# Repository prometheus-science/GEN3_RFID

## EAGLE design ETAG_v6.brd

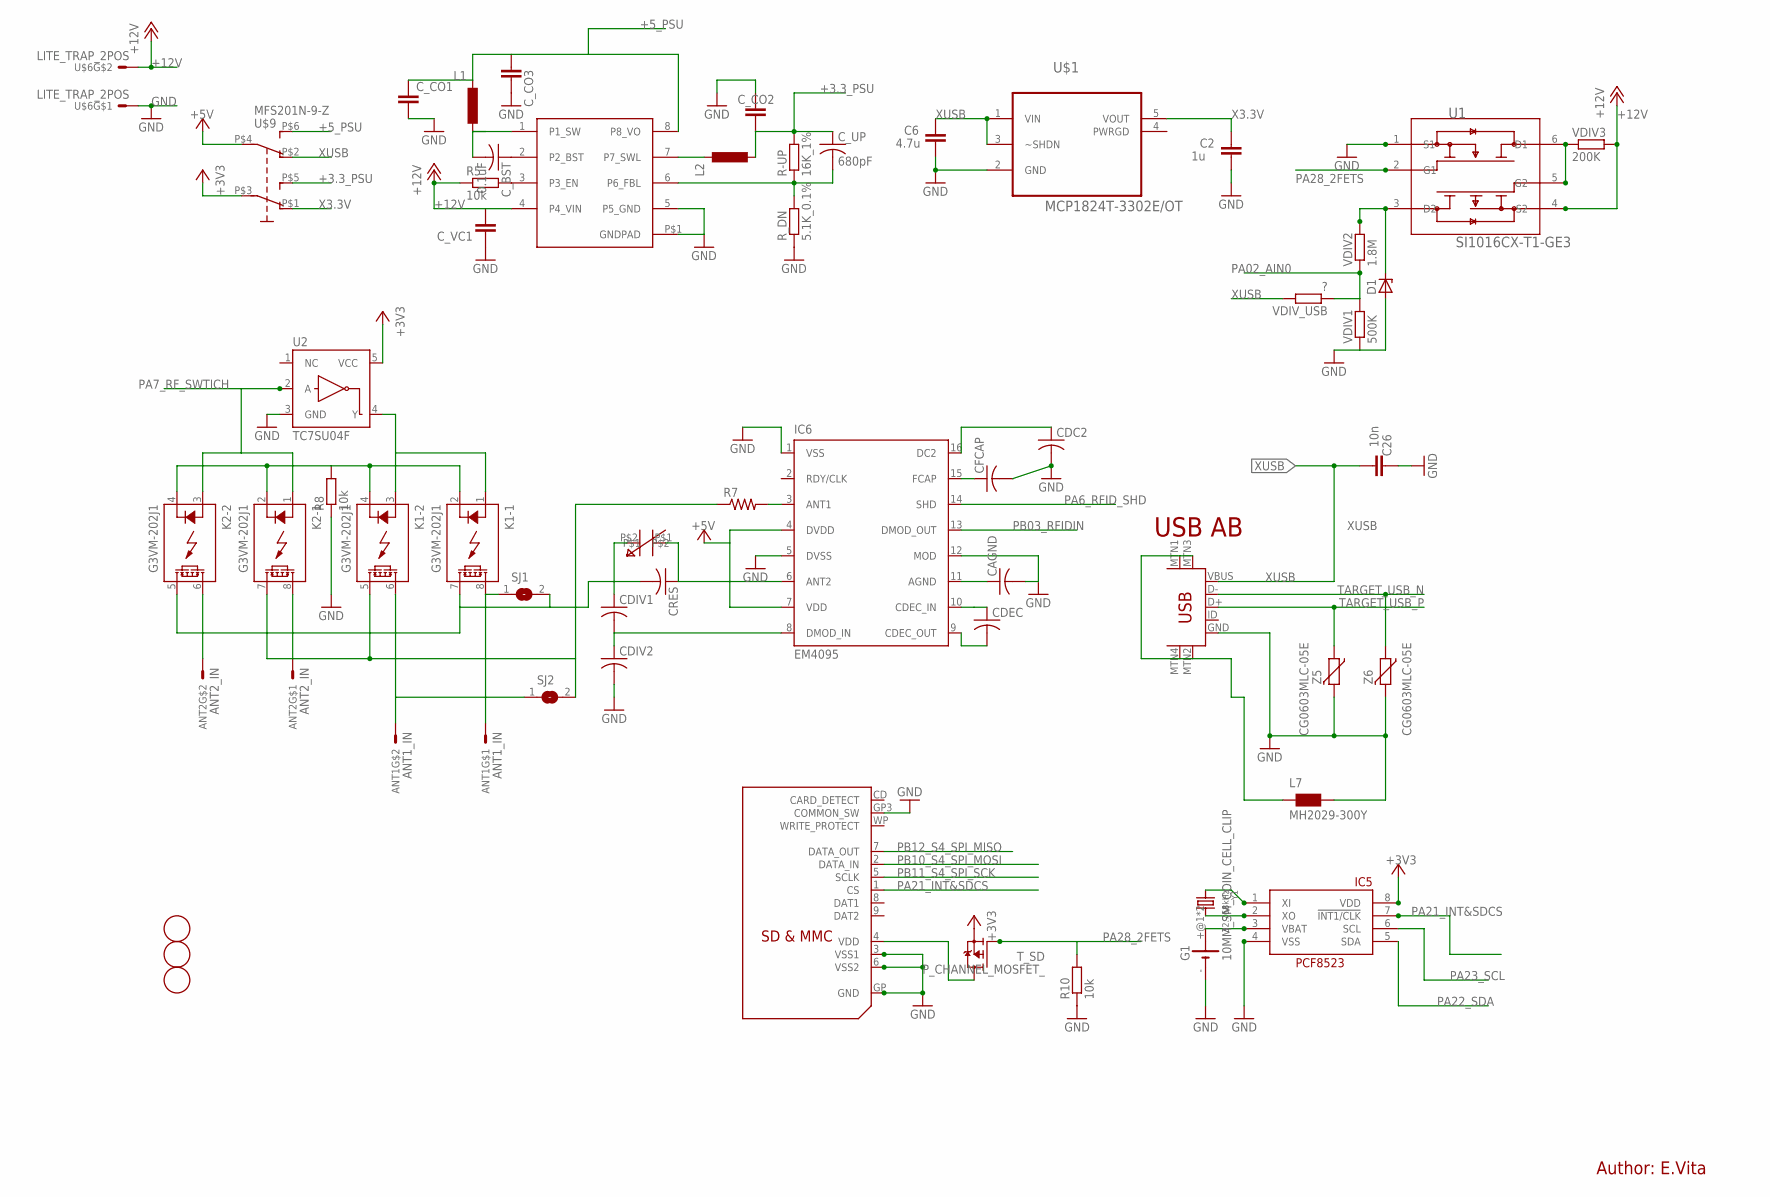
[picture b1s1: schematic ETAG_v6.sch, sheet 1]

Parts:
ANT1: ANT1_IN; LITE_TRAP_MINI
ANT2: ANT2_IN; LITE_TRAP_MINI
C2: 1u; C0603-ROUND
C6: 4.7u; C0603-ROUND
C26: 10n; C0603-ROUND
CAGND: C-US; C0603-ROUND
CDC2: C-US; C0603-ROUND
CDEC: C-US; C0603-ROUND
CDIV1, CDIV2: C-USC1206K; C1206K
CFCAP: C-US; C0603-ROUND
CRES: C-USC1206K; C1206K
C_BST: 0.1uF; C0603-ROUND
C_CO1, C_CO2: 22uF; C0805
C_CO3: 10uF; C0805
C_UP: 680pF; C0603-ROUND
C_VC1: 10uF; C1210
D1: ZENER-DIODESOD123; SOD123FL
FD1, FD2, FD3: FIDUCIALMOUNT; FIDUCIA-MOUNT
G1: 10MM_SM_COIN_CELL_CLIP
IC5: RTC_PCF8523T; SOIC8_150MIL
IC6: EM4095; SO16
K1, K2: G3VM-202J1; SOP08
L1: 22uH; SLF10165
L2: 2.2uH; L1008(2520METRIC)
L7: MH2029-300Y; 0805
R5, R8, R10: 10k; R0603-ROUND
R7: R-US_R1206; R1206
R-UP: 16K_1%; R0603-ROUND
R_DN: 5.1K_0.1%; R0603-ROUND
SJ1, SJ2: SJW
T_SD: P_CHANNEL_MOSFET_; SOT23
U1: SI1016CX-T1-GE3; SOT50P162X60-6N
U2: TC7SU04F; SOT23-5
U$1: MCP1824T-3302E/OT; SOT95P270X145-5N
U$3: BD93291EFJSOP8_W_GND; SOP08_GNDPAD
U$4: SDMMC06132; 06132
U$5: USB-MINIB-5PIN; USB-MINIB
U$6: LITE_TRAP_2POS; LITE_TRAP_MINI
U$9: MFS201N-9-Z
VAR_C: TZB4Z100AB10R00
VDIV1: 500K; R0603-ROUND
VDIV2: 1.8M; R0603-ROUND
VDIV3: 200K; R0603-ROUND
VDIV_USB: ?; R0603-ROUND
Y1: 32.768kHz; CRYSTAL_8X3.8
Z5, Z6: CG0603MLC-05E; CT/CN0603

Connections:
2GND: L7.1, U$5.MTN1 (MTN2), U$5.MTN2 (MTN3), U$5.MTN3 (MTN1), U$5.MTN4
+3.3_PSU: C_CO2.2, C_UP.1, L2.2, R-UP.2, U$9.P$5 (S)
+3V3: IC5.8 (VDD), T_SD.2 (S), U2.5 (VCC), U$9.P$3; also elsewhere on the board
+5V: IC6.4 (DVDD), IC6.7 (VDD), U$9.P$4 (P1); also elsewhere on the board
+5_PSU: C_CO1.1, C_CO3.1, L1.P$1 (1), U$3.8 (P8_VO), U$9.P$6 (S1)
+12V: C_VC1.2, R5.1, U1.4 (S2), U$3.4 (P4_VIN), U$6.P$3, U$6.P$4, VDIV3.2; also elsewhere on the board
GND: C2.1, C6.1, C26.2, CAGND.2, CDC2.2, CDIV2.2, CFCAP.2, C_CO1.2, C_CO2.1, C_CO3.2, C_VC1.1, D1.A, G1.-, IC5.4 (VSS), IC6.1 (VSS), IC6.5 (DVSS), IC6.12 (MOD), L7.2, R8.1, R10.1, R_DN.1, U1.1 (S1), U2.3 (GND), U$1.2 (GND), U$3.5 (P5_GND), U$3.P$1 (GNDPAD), U$4.3 (VSS1), U$4.6 (VSS2), U$4.GP (GND), U$4.GP3 (COMMON_SW), U$5.GND, U$6.P$1, U$6.P$2, VDIV1.1, Z5.2, Z6.2; also elsewhere on the board
unnamed: IC5.2 (XO), Y1.P$4 (2)
unnamed: IC5.1 (XI), Y1.P$1 (1)
unnamed: CFCAP.1, IC6.15 (FCAP)
unnamed: CAGND.1, IC6.11 (AGND)
unnamed: C_BST.1, U$3.2 (P2_BST)
unnamed: C_UP.2, R-UP.1, R_DN.2, U$3.6 (P6_FBL)
unnamed: R5.2, U$3.3 (P3_EN)
unnamed: K1.5 (D2), K2.7 (D2), R7.1, SJ2.2
unnamed: CDIV1.1, CRES.2, K1.7 (D2), K2.5 (D2), SJ1.2, VAR_C.P$2
unnamed: CRES.1, IC6.6 (ANT2), VAR_C.P$1
unnamed: CDIV1.2, CDIV2.1, IC6.8 (DMOD_IN)
unnamed: ANT1.P$1, ANT1.P$2, K1.8 (D1), SJ1.1
unnamed: U1.5 (G2), U1.6 (D1), VDIV3.1
unnamed: ANT2.P$1, ANT2.P$2, K2.8 (D1)
unnamed: CDC2.1, IC6.16 (DC2)
unnamed: CDEC.2, IC6.9 (CDEC_OUT)
unnamed: CDEC.1, IC6.10 (CDEC_IN)
unnamed: IC6.3 (ANT1), R7.2
unnamed: D1.C, U1.3 (D2), VDIV2.2
unnamed: K1.2 (K), K1.4 (K), K2.2 (K), K2.4 (K), R8.2
unnamed: L2.1, U$3.7 (P7_SWL)
unnamed: C_BST.2, L1.P$2 (2), U$3.1 (P1_SW)
unnamed: ANT2.P$3, ANT2.P$4, K2.6 (D1)
unnamed: K1.1 (A), K1.3 (A), U2.4 (Y)
unnamed: ANT1.P$3, ANT1.P$4, K1.6 (D1), SJ2.1
PA02_AIN0: VDIV1.2, VDIV2.1, VDIV_USB.1; also elsewhere on the board
PA6_RFID_SHD: IC6.14 (SHD)
PA7_RF_SWTICH: K2.1 (A), K2.3 (A), U2.2 (A); also elsewhere on the board
PA21_INT&SDCS: IC5.7 (!INT1/CLK), U$4.1 (CS); also elsewhere on the board
PA22_SDA: IC5.5 (SDA); also elsewhere on the board
PA23_SCL: IC5.6 (SCL); also elsewhere on the board
PA28_2FETS: R10.2, T_SD.1 (G), U1.2 (G1); also elsewhere on the board
PB03_RFIDIN: IC6.13 (DMOD_OUT); also elsewhere on the board
PB10_S4_SPI_MOSI: U$4.2 (DATA_IN); also elsewhere on the board
PB11_S4_SPI_SCK: U$4.5 (SCLK); also elsewhere on the board
PB12_S4_SPI_MISO: U$4.7 (DATA_OUT); also elsewhere on the board
TARGET_USB_N: U$5.D-, Z6.1; also elsewhere on the board
TARGET_USB_P: U$5.D+, Z5.1; also elsewhere on the board
VBAT1: G1.+@1 (+), G1.+@2 (+), IC5.3 (VBAT)
VDD: T_SD.3 (D), U$4.4 (VDD)
X3.3V: C2.2, U$1.5 (VOUT), U$9.P$1 (O)
XUSB: C6.2, C26.1, U$1.1 (VIN), U$1.3 (~SHDN), U$5.VBUS, U$9.P$2 (O1), VDIV_USB.2

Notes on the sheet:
USB AB
Author: E.Vita

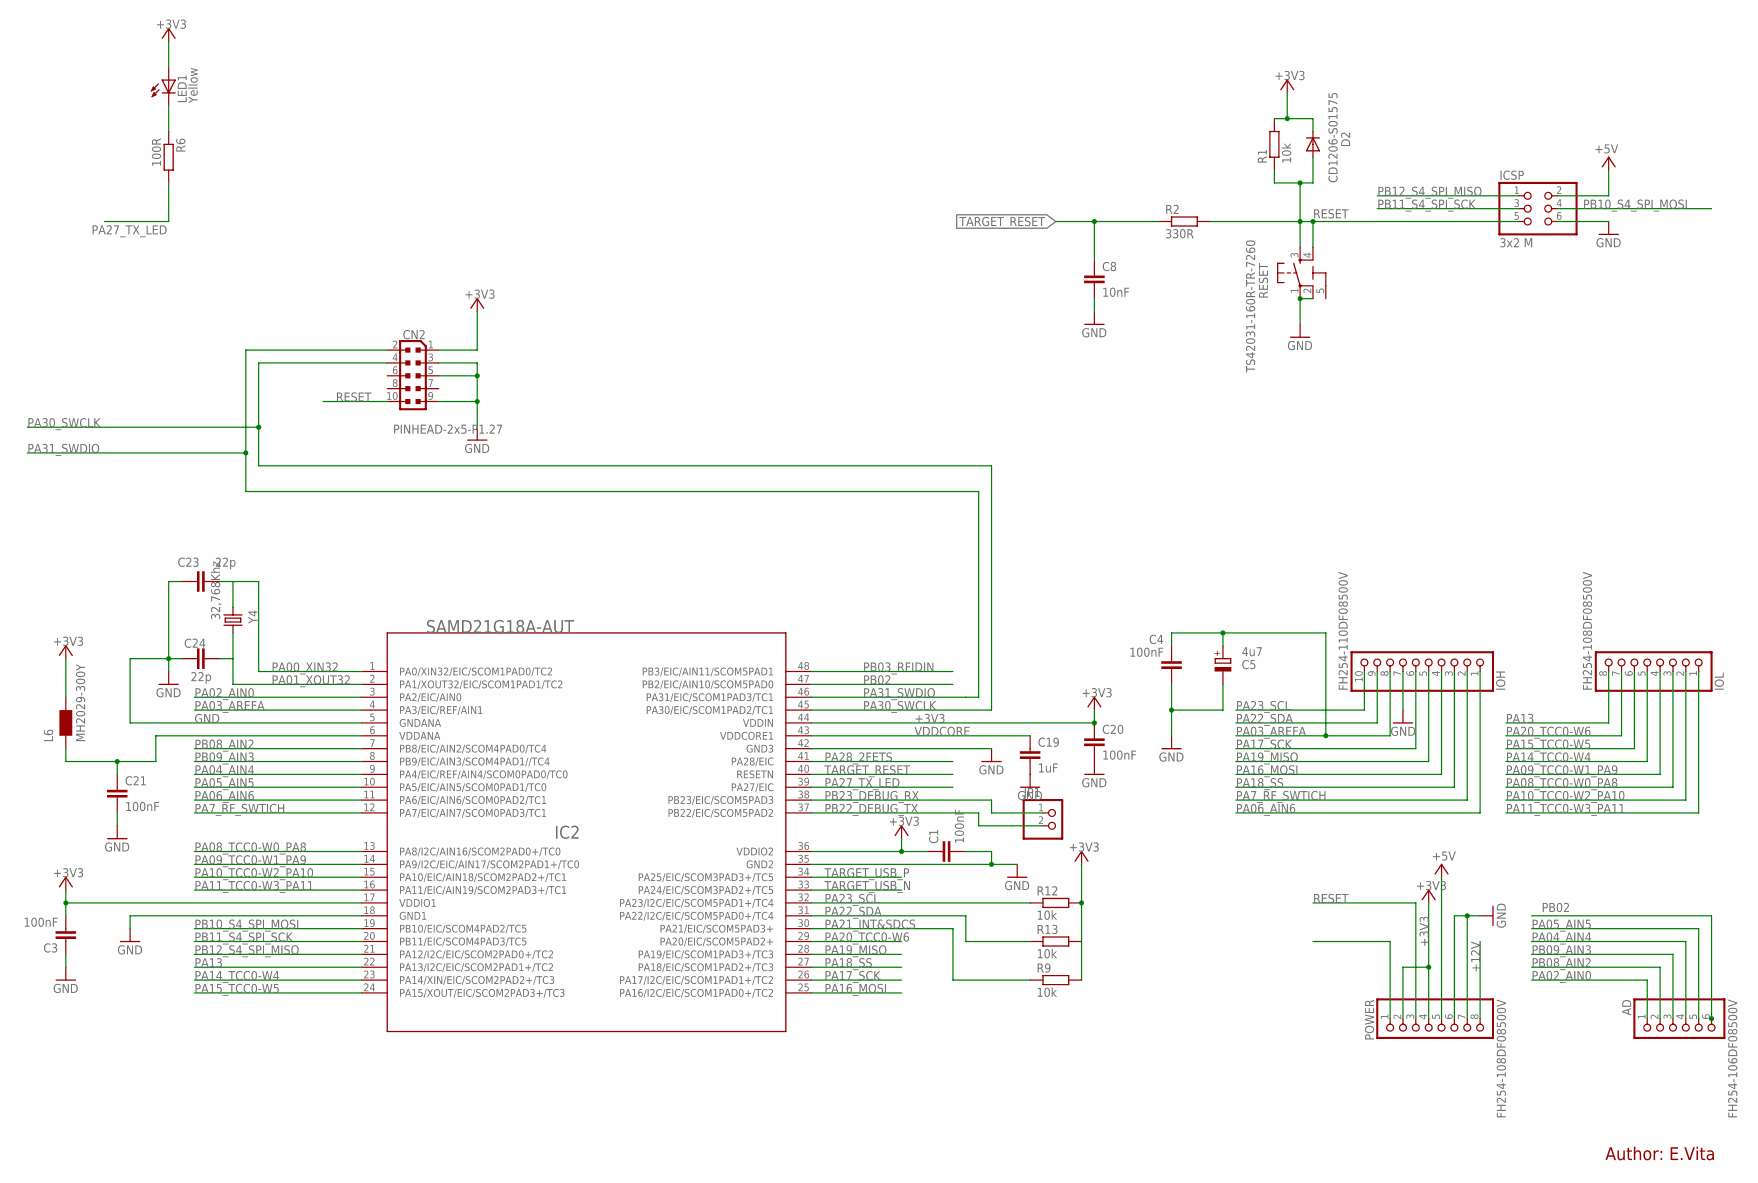
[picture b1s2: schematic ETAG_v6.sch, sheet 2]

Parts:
AD: FH254-106DF08500V; 1X06
C1, C3, C4, C20, C21: 100nF; C0603-ROUND
C5: 4u7; SMC_A
C8: 10nF; C0603-ROUND
C19: 1uF; C0603-ROUND
C23, C24: 22p; C0603-ROUND
CN2: PINHEAD-2x5-P1.27; PINHEAD_2X05_127
D2: CD1206-S01575; MINIMELF
IC2: SAMD21G18A-AUT; TQFP48-7X7
ICSP: 3x2 M; 2X03
IOH: FH254-110DF08500V; 1X10
IOL: FH254-108DF08500V; 1X08
JP1: PINHD-1X2; 1X02
L6: MH2029-300Y; 0805
LED1: Yellow; CHIPLED_0805
POWER: FH254-108DF08500V; 1X08
R1, R9, R12, R13: 10k; R0603-ROUND
R2: 330R; R0603-ROUND
R6: 100R; R0603-ROUND
RESET: TS42031-160R-TR-7260; TS42
Y4: 32,768Khz; RESONATOR_EPSON_FC_145

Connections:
5-GND: RESET.5 (5-GND)
+3V3: C1.1, C3.2, C20.1, CN2.1, D2.C, IC2.17 (VDDIO1), IC2.36 (VDDIO2), IC2.44 (VDDIN), L6.2, LED1.A, POWER.2, POWER.4, R1.2, R9.2, R12.2, R13.2; also elsewhere on the board
+5V: ICSP.2, POWER.5; also elsewhere on the board
+12V: POWER.8; also elsewhere on the board
GND: C1.2, C3.1, C4.2, C5.-, C8.2, C19.2, C20.2, C21.2, C23.1, C24.1, CN2.3, CN2.5, CN2.9, IC2.5 (GNDANA), IC2.18 (GND1), IC2.35 (GND2), IC2.42 (GND3), ICSP.6, IOH.7, POWER.6, POWER.7, RESET.1, RESET.2; also elsewhere on the board
unnamed: LED1.C, R6.1
unnamed: C21.1, IC2.6 (VDDANA), L6.1
PA00_XIN32: C23.2, IC2.1 (PA0/XIN32/EIC/SCOM1PAD0/TC2), Y4.P$1 (1)
PA01_XOUT32: C24.2, IC2.2 (PA1/XOUT32/EIC/SCOM1PAD1/TC2), Y4.P$2 (2)
PA02_AIN0: AD.1, IC2.3 (PA2/EIC/AIN0); also elsewhere on the board
PA03_AREFA: C4.1, C5.+, IC2.4 (PA3/EIC/REF/AIN1), IOH.8
PA04_AIN4: AD.4, IC2.9 (PA4/EIC/REF/AIN4/SCOM0PAD0/TC0)
PA05_AIN5: AD.5, IC2.10 (PA5/EIC/AIN5/SCOM0PAD1/TC0)
PA06_AIN6: IC2.11 (PA6/EIC/AIN6/SCOM0PAD2/TC1), IOH.1
PA7_RF_SWTICH: IC2.12 (PA7/EIC/AIN7/SCOM0PAD3/TC1), IOH.2; also elsewhere on the board
PA08_TCC0-W0_PA8: IC2.13 (PA8/I2C/AIN16/SCOM2PAD0+/TC0), IOL.3
PA09_TCC0-W1_PA9: IC2.14 (PA9/I2C/EIC/AIN17/SCOM2PAD1+/TC0), IOL.4
PA10_TCC0-W2_PA10: IC2.15 (PA10/EIC/AIN18/SCOM2PAD2+/TC1), IOL.2
PA11_TCC0-W3_PA11: IC2.16 (PA11/EIC/AIN19/SCOM2PAD3+/TC1), IOL.1
PA13: IC2.22 (PA13/I2C/EIC/SCOM2PAD1+/TC2), IOL.8
PA14_TCC0-W4: IC2.23 (PA14/XIN/EIC/SCOM2PAD2+/TC3), IOL.5
PA15_TCC0-W5: IC2.24 (PA15/XOUT/EIC/SCOM2PAD3+/TC3), IOL.6
PA16_MOSI: IC2.25 (PA16/I2C/EIC/SCOM1PAD0+/TC2), IOH.4
PA17_SCK: IC2.26 (PA17/I2C/EIC/SCOM1PAD1+/TC2), IOH.6
PA18_SS: IC2.27 (PA18/EIC/SCOM1PAD2+/TC3), IOH.3
PA19_MISO: IC2.28 (PA19/EIC/SCOM1PAD3+/TC3), IOH.5
PA20_TCC0-W6: IC2.29 (PA20/EIC/SCOM5PAD2+), IOL.7
PA21_INT&SDCS: IC2.30 (PA21/EIC/SCOM5PAD3+), R9.1; also elsewhere on the board
PA22_SDA: IC2.31 (PA22/I2C/EIC/SCOM5PAD0+/TC4), IOH.9, R13.1; also elsewhere on the board
PA23_SCL: IC2.32 (PA23/I2C/EIC/SCOM5PAD1+/TC4), IOH.10, R12.1; also elsewhere on the board
PA27_TX_LED: IC2.39 (PA27/EIC), R6.2
PA28_2FETS: IC2.41 (PA28/EIC); also elsewhere on the board
PA30_SWCLK: CN2.4, IC2.45 (PA30/EIC/SCOM1PAD2/TC1)
PA31_SWDIO: CN2.2, IC2.46 (PA31/EIC/SCOM1PAD3/TC1)
PB02: AD.6, IC2.47 (PB2/EIC/AIN10/SCOM5PAD0)
PB03_RFIDIN: IC2.48 (PB3/EIC/AIN11/SCOM5PAD1); also elsewhere on the board
PB08_AIN2: AD.2, IC2.7 (PB8/EIC/AIN2/SCOM4PAD0/TC4)
PB09_AIN3: AD.3, IC2.8 (PB9/EIC/AIN3/SCOM4PAD1//TC4)
PB10_S4_SPI_MOSI: IC2.19 (PB10/EIC/SCOM4PAD2/TC5), ICSP.4; also elsewhere on the board
PB11_S4_SPI_SCK: IC2.20 (PB11/EIC/SCOM4PAD3/TC5), ICSP.3; also elsewhere on the board
PB12_S4_SPI_MISO: IC2.21 (PA12/I2C/EIC/SCOM2PAD0+/TC2), ICSP.1; also elsewhere on the board
PB22_DEBUG_TX: IC2.37 (PB22/EIC/SCOM5PAD2), JP1.2
PB23_DEBUG_RX: IC2.38 (PB23/EIC/SCOM5PAD3), JP1.1
RESET: CN2.10, D2.A, ICSP.5, POWER.3, R1.1, R2.2, RESET.3, RESET.4
TARGET_RESET: C8.1, IC2.40 (RESETN), R2.1
TARGET_USB_N: IC2.33 (PA24/EIC/SCOM3PAD2+/TC5); also elsewhere on the board
TARGET_USB_P: IC2.34 (PA25/EIC/SCOM3PAD3+/TC5); also elsewhere on the board
VDDCORE: C19.1, IC2.43 (VDDCORE1)

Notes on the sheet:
Author: E.Vita

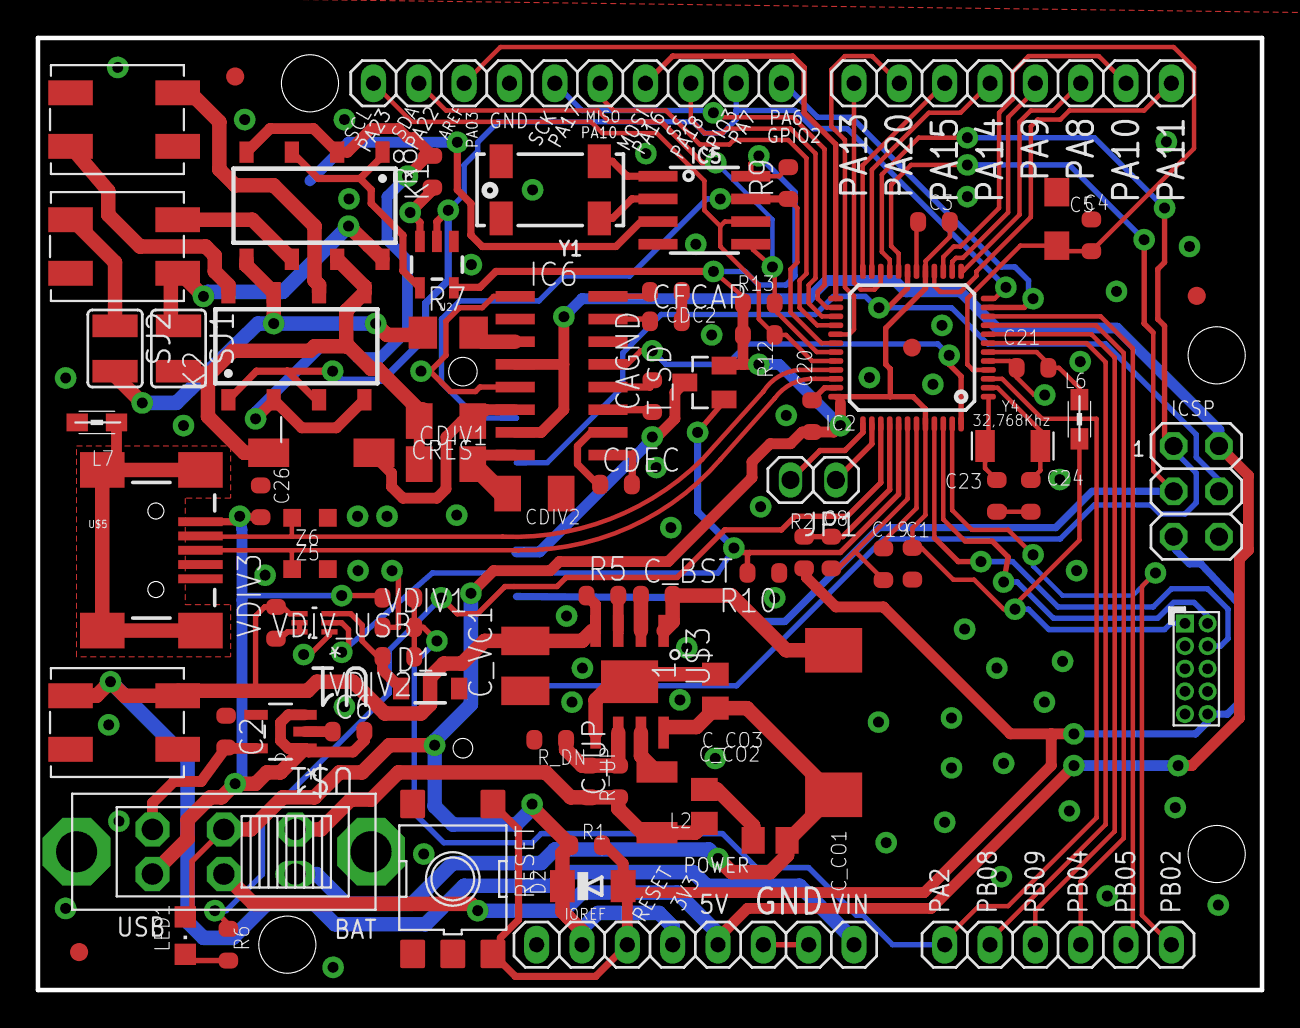
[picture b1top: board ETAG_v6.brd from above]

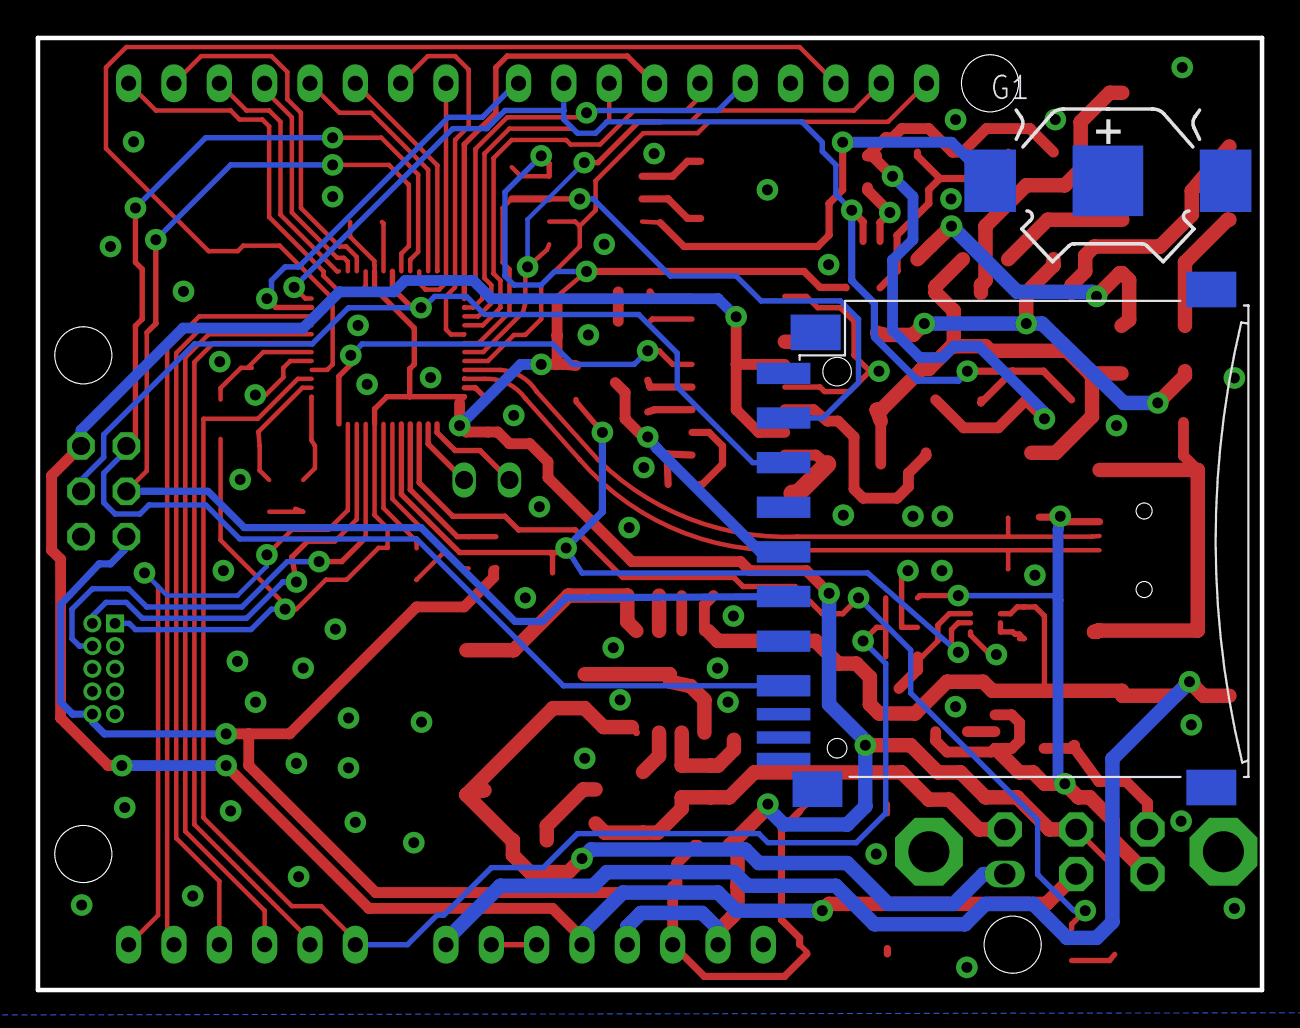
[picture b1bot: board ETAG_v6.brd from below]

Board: 4 copper layers, 68.6 x 53.3 mm, 84 parts (2 on the bottom side), 79 nets.

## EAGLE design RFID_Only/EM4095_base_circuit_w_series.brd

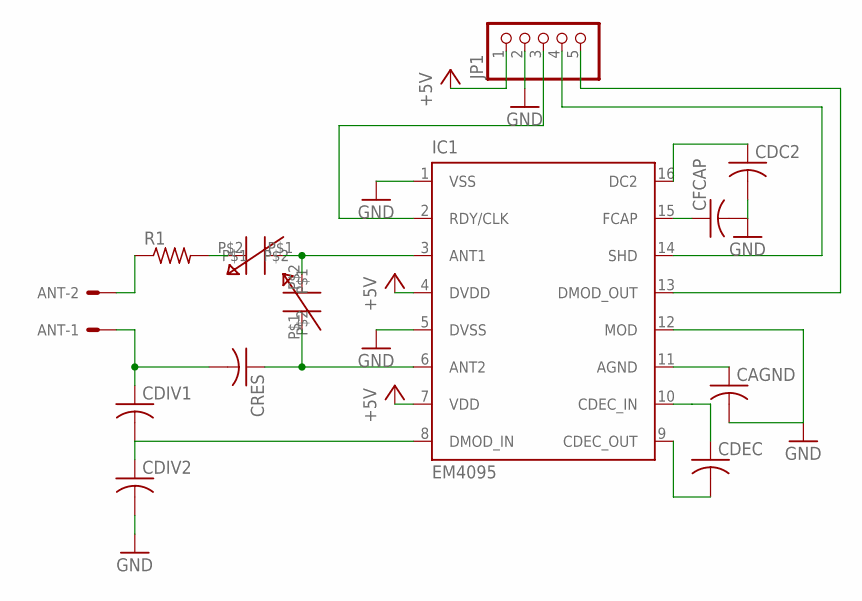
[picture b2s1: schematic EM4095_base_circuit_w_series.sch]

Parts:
ANT: KK-156-2
CAGND: C-USC1206K; C1206K
CDC2: C-USC1206K; C1206K
CDEC: C-USC1206K; C1206K
CDIV1, CDIV2: C-USC1206K; C1206K
CFCAP: C-USC1206K; C1206K
CRES: C-USC1206K; C1206K
IC1: EM4095; SO16
JP1: PINHD-1X5; 1X05
R1: R-US_R1206; R1206
U$1, U$2: TZB4Z100AB10R00

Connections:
+5V: IC1.4 (DVDD), IC1.7 (VDD), JP1.1
DMOD: IC1.13 (DMOD_OUT), JP1.5
GND: CAGND.2, CDC2.2, CDIV2.2, CFCAP.2, IC1.1 (VSS), IC1.5 (DVSS), IC1.12 (MOD), JP1.2
unnamed: CFCAP.1, IC1.15 (FCAP)
unnamed: CAGND.1, IC1.11 (AGND)
unnamed: CRES.1, IC1.6 (ANT2), U$1.P$1
unnamed: CDIV1.2, CDIV2.1, IC1.8 (DMOD_IN)
unnamed: ANT.1, CDIV1.1, CRES.2
unnamed: R1.2, U$2.P$2
unnamed: IC1.3 (ANT1), U$1.P$2, U$2.P$1
unnamed: CDC2.1, IC1.16 (DC2)
unnamed: ANT.2, R1.1
unnamed: CDEC.2, IC1.9 (CDEC_OUT)
unnamed: CDEC.1, IC1.10 (CDEC_IN)
RDY: IC1.2 (RDY/CLK), JP1.3
SLP: IC1.14 (SHD), JP1.4

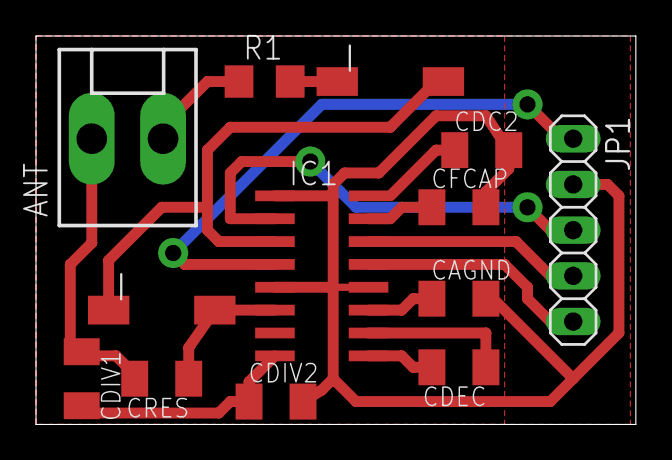
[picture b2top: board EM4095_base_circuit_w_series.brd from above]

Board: 2 copper layers, 33.3 x 21.6 mm, 13 parts (0 on the bottom side), 16 nets.

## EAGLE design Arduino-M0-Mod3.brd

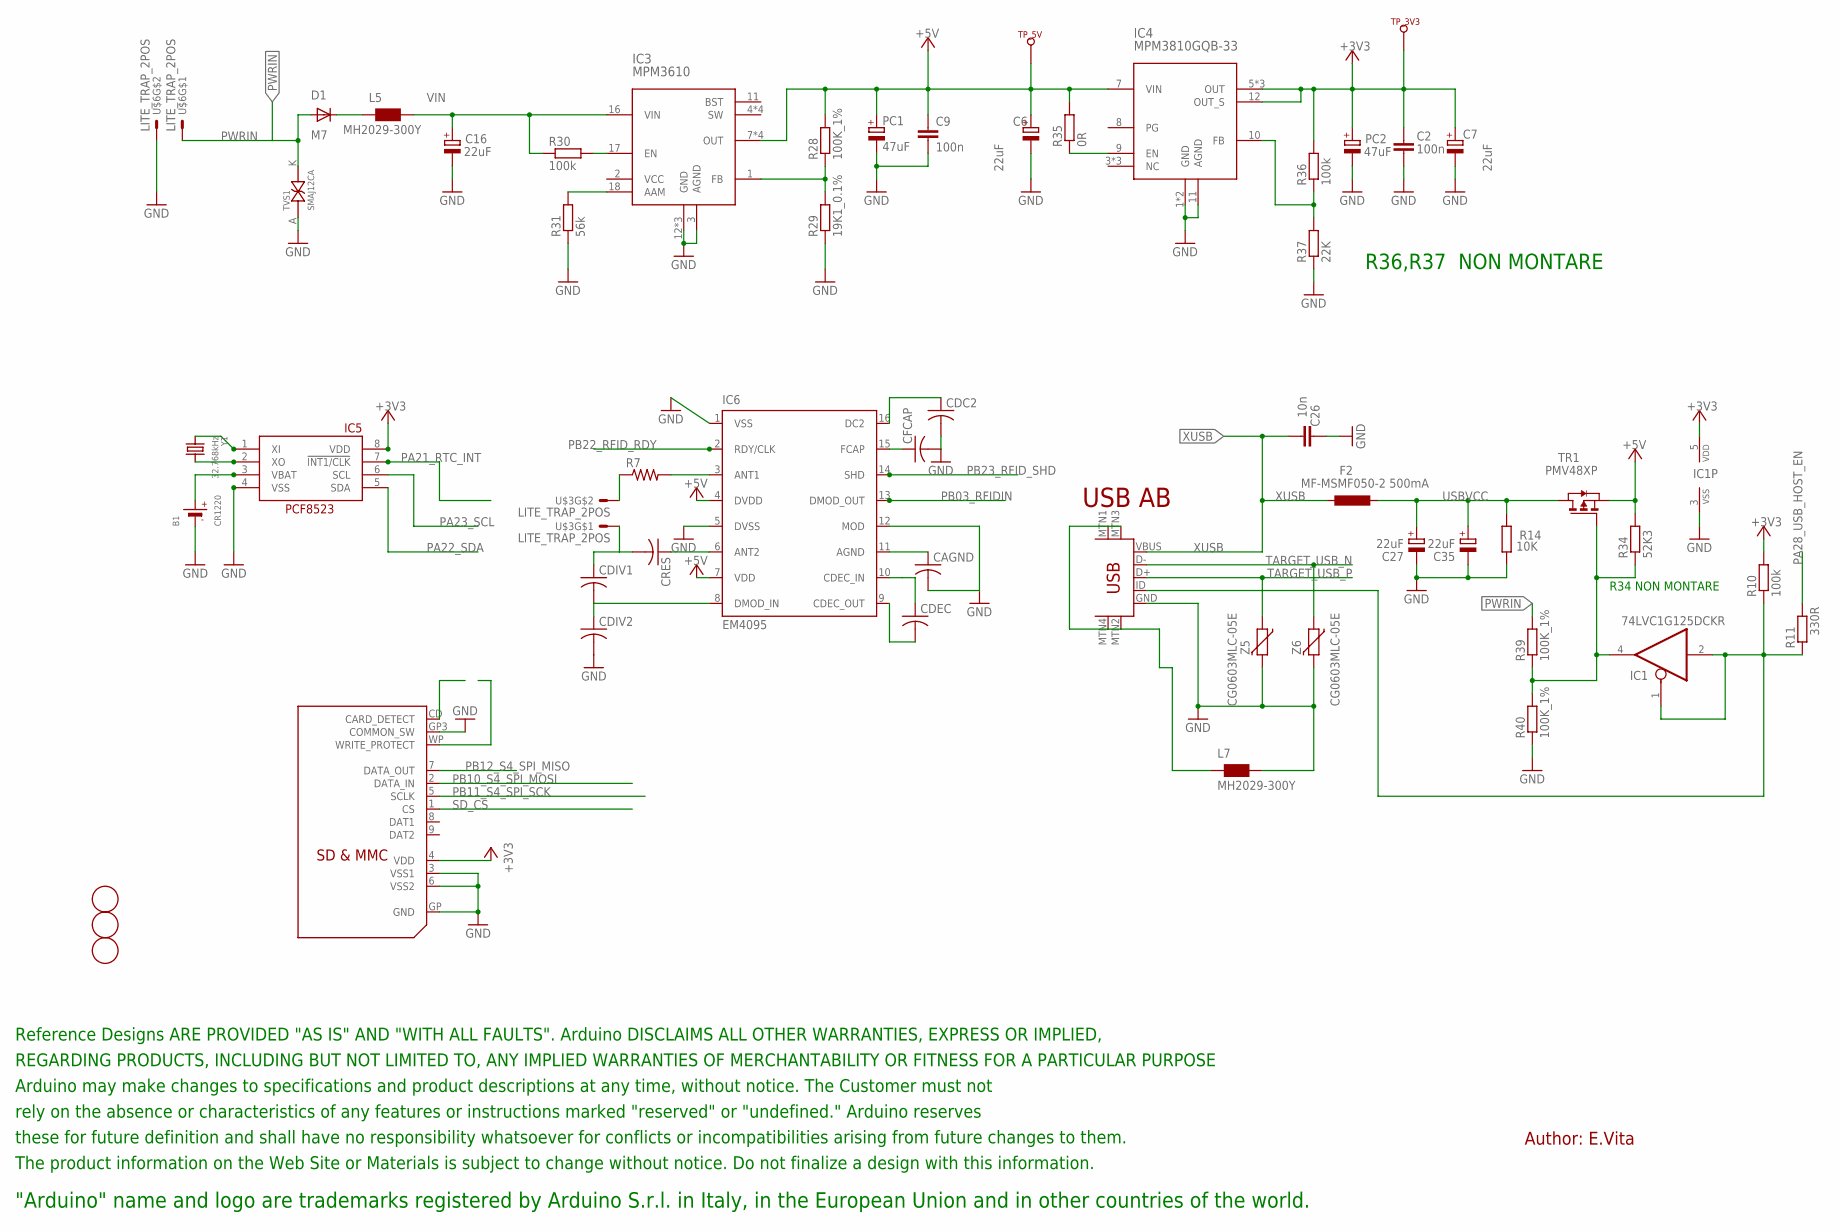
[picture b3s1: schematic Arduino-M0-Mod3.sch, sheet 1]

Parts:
B1: CR1220
C2, C9: 100n; C0603-ROUND
C6, C7, C16, C27, C35: 22uF; SMC_B
C26: 10n; C0603-ROUND
CAGND: C-USC1206K; C1206K
CDC2: C-USC1206K; C1206K
CDEC: C-USC1206K; C1206K
CDIV1, CDIV2: C-USC1206K; C1206K
CFCAP: C-USC1206K; C1206K
CRES: C-USC1206K; C1206K
D1: M7; SMB
F2: MF-MSMF050-2 500mA; L1812
FD1, FD2, FD3: FIDUCIALMOUNT; FIDUCIA-MOUNT
IC1: 74LVC1G125DCKR; SC70-5
IC3: MPM3610; QFN-20
IC4: MPM3810GQB-33; QFN-12
IC5: RTC_PCF8523T; SOIC8_150MIL
IC6: EM4095; SO16
L5, L7: MH2029-300Y; 0805
PC1, PC2: 47uF; PANASONIC_D
R7: R-US_R1206; R1206
R10, R30, R36: 100k; R0603-ROUND
R11: 330R; R0603-ROUND
R14: 10K; R0603-ROUND
R28, R39, R40: 100K_1%; R0603-ROUND
R29: 19K1_0.1%; R0603-ROUND
R31: 56k; R0603-ROUND
R34: 52K3; R0603-ROUND
R35: 0R; R0603-ROUND
R37: 22K; R0603-ROUND
TP_3V3, TP_5V: TP_SP; TP-SP
TR1: PMV48XP; SOT-23
TVS1: SMAJ12CA; SMA-TVS
U$1: DISCLAIMER-SMALL; DISCLAIMER
U$3, U$6: LITE_TRAP_2POS; LITE_TRAP_MINI
U$4: SDMMC06132; 06132
U$5: USB-MINIB-5PIN; USB-MINIB
Y1: 32.768kHz; CRYSTAL_8X3.8
Z5, Z6: CG0603MLC-05E; CT/CN0603

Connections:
2GND: L7.1, U$5.MTN1 (MTN2), U$5.MTN2 (MTN3), U$5.MTN3 (MTN1), U$5.MTN4
+3V3: C2.2, C7.+, IC1.5 (VDD), IC4.5 (OUT), IC4.6 (OUT), IC4.12 (OUT_S), IC4.14 (OUT), IC5.8 (VDD), PC2.+, R10.2, R36.2, TP_3V3.X, U$4.4 (VDD); also elsewhere on the board
+5V: C6.+, C9.1, IC3.7 (OUT), IC3.8 (OUT), IC3.9 (OUT), IC3.20 (OUT), IC4.7 (VIN), IC6.4 (DVDD), IC6.7 (VDD), PC1.+, R28.2, R34.2, R35.2, TP_5V.X, TR1.2 (S); also elsewhere on the board
GND: B1.-, C2.1, C6.-, C7.-, C9.2, C16.-, C26.2, C27.-, C35.-, CAGND.2, CDC2.2, CDIV2.2, CFCAP.2, IC1.3 (VSS), IC3.3 (AGND), IC3.12 (GND), IC3.13 (GND), IC3.14 (GND), IC4.1 (GND), IC4.2 (GND), IC4.11 (AGND), IC5.4 (VSS), IC6.1 (VSS), IC6.5 (DVSS), IC6.12 (MOD), L7.2, PC1.-, PC2.-, R14.1, R29.1, R31.1, R37.1, R40.1, TVS1.A (AK), U$4.3 (VSS1), U$4.6 (VSS2), U$4.GP (GND), U$4.GP3 (COMMON_SW), U$5.GND, U$6.P$3, U$6.P$4, Z5.2, Z6.2; also elsewhere on the board
unnamed: IC5.2 (XO), Y1.P$4 (2)
unnamed: IC5.1 (XI), Y1.P$1 (1)
unnamed: CFCAP.1, IC6.15 (FCAP)
unnamed: CAGND.1, IC6.11 (AGND)
unnamed: IC1.4 (O), R34.1, R39.1, R40.2, TR1.3 (G)
unnamed: IC1.1 (OE), IC1.2 (I), R10.1, R11.1, U$5.ID
unnamed: D1.C, L5.1
unnamed: IC4.9 (EN), R35.1
unnamed: IC4.10 (FB), R36.1, R37.2
unnamed: CRES.1, IC6.6 (ANT2)
unnamed: CDIV1.2, CDIV2.1, IC6.8 (DMOD_IN)
unnamed: R7.1, U$3.P$3, U$3.P$4
unnamed: CDIV1.1, CRES.2, U$3.P$1, U$3.P$2
unnamed: CDC2.1, IC6.16 (DC2)
unnamed: CDEC.2, IC6.9 (CDEC_OUT)
unnamed: CDEC.1, IC6.10 (CDEC_IN)
unnamed: IC6.3 (ANT1), R7.2
unnamed: IC3.1 (FB), R28.1, R29.2
unnamed: IC3.17 (EN), R30.2
unnamed: IC3.18 (AAM), R31.2
PA21_RTC_INT: IC5.7 (!INT1/CLK); also elsewhere on the board
PA22_SDA: IC5.5 (SDA); also elsewhere on the board
PA23_SCL: IC5.6 (SCL); also elsewhere on the board
PA28_USB_HOST_EN: R11.2; also elsewhere on the board
PB03_RFIDIN: IC6.13 (DMOD_OUT); also elsewhere on the board
PB10_S4_SPI_MOSI: U$4.2 (DATA_IN); also elsewhere on the board
PB11_S4_SPI_SCK: U$4.5 (SCLK); also elsewhere on the board
PB12_S4_SPI_MISO: U$4.7 (DATA_OUT); also elsewhere on the board
PB22_RFID_RDY: IC6.2 (RDY/CLK); also elsewhere on the board
PB23_RFID_SHD: IC6.14 (SHD); also elsewhere on the board
PWRIN: D1.A, R39.2, TVS1.K (KA), U$6.P$1, U$6.P$2; also elsewhere on the board
SD_CD: U$4.CD (CARD_DETECT)
SD_WP: U$4.WP (WRITE_PROTECT)
TARGET_USB_N: U$5.D-, Z6.1; also elsewhere on the board
TARGET_USB_P: U$5.D+, Z5.1; also elsewhere on the board
USBVCC: C27.+, C35.+, F2.1, R14.2, TR1.1 (D)
VBAT1: B1.+$1 (+), IC5.3 (VBAT)
VIN: C16.+, IC3.16 (VIN), L5.2, R30.1
XUSB: C26.1, F2.2, U$5.VBUS

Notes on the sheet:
USB AB
R34 NON MONTARE
R36,R37 NON MONTARE
Author: E.Vita

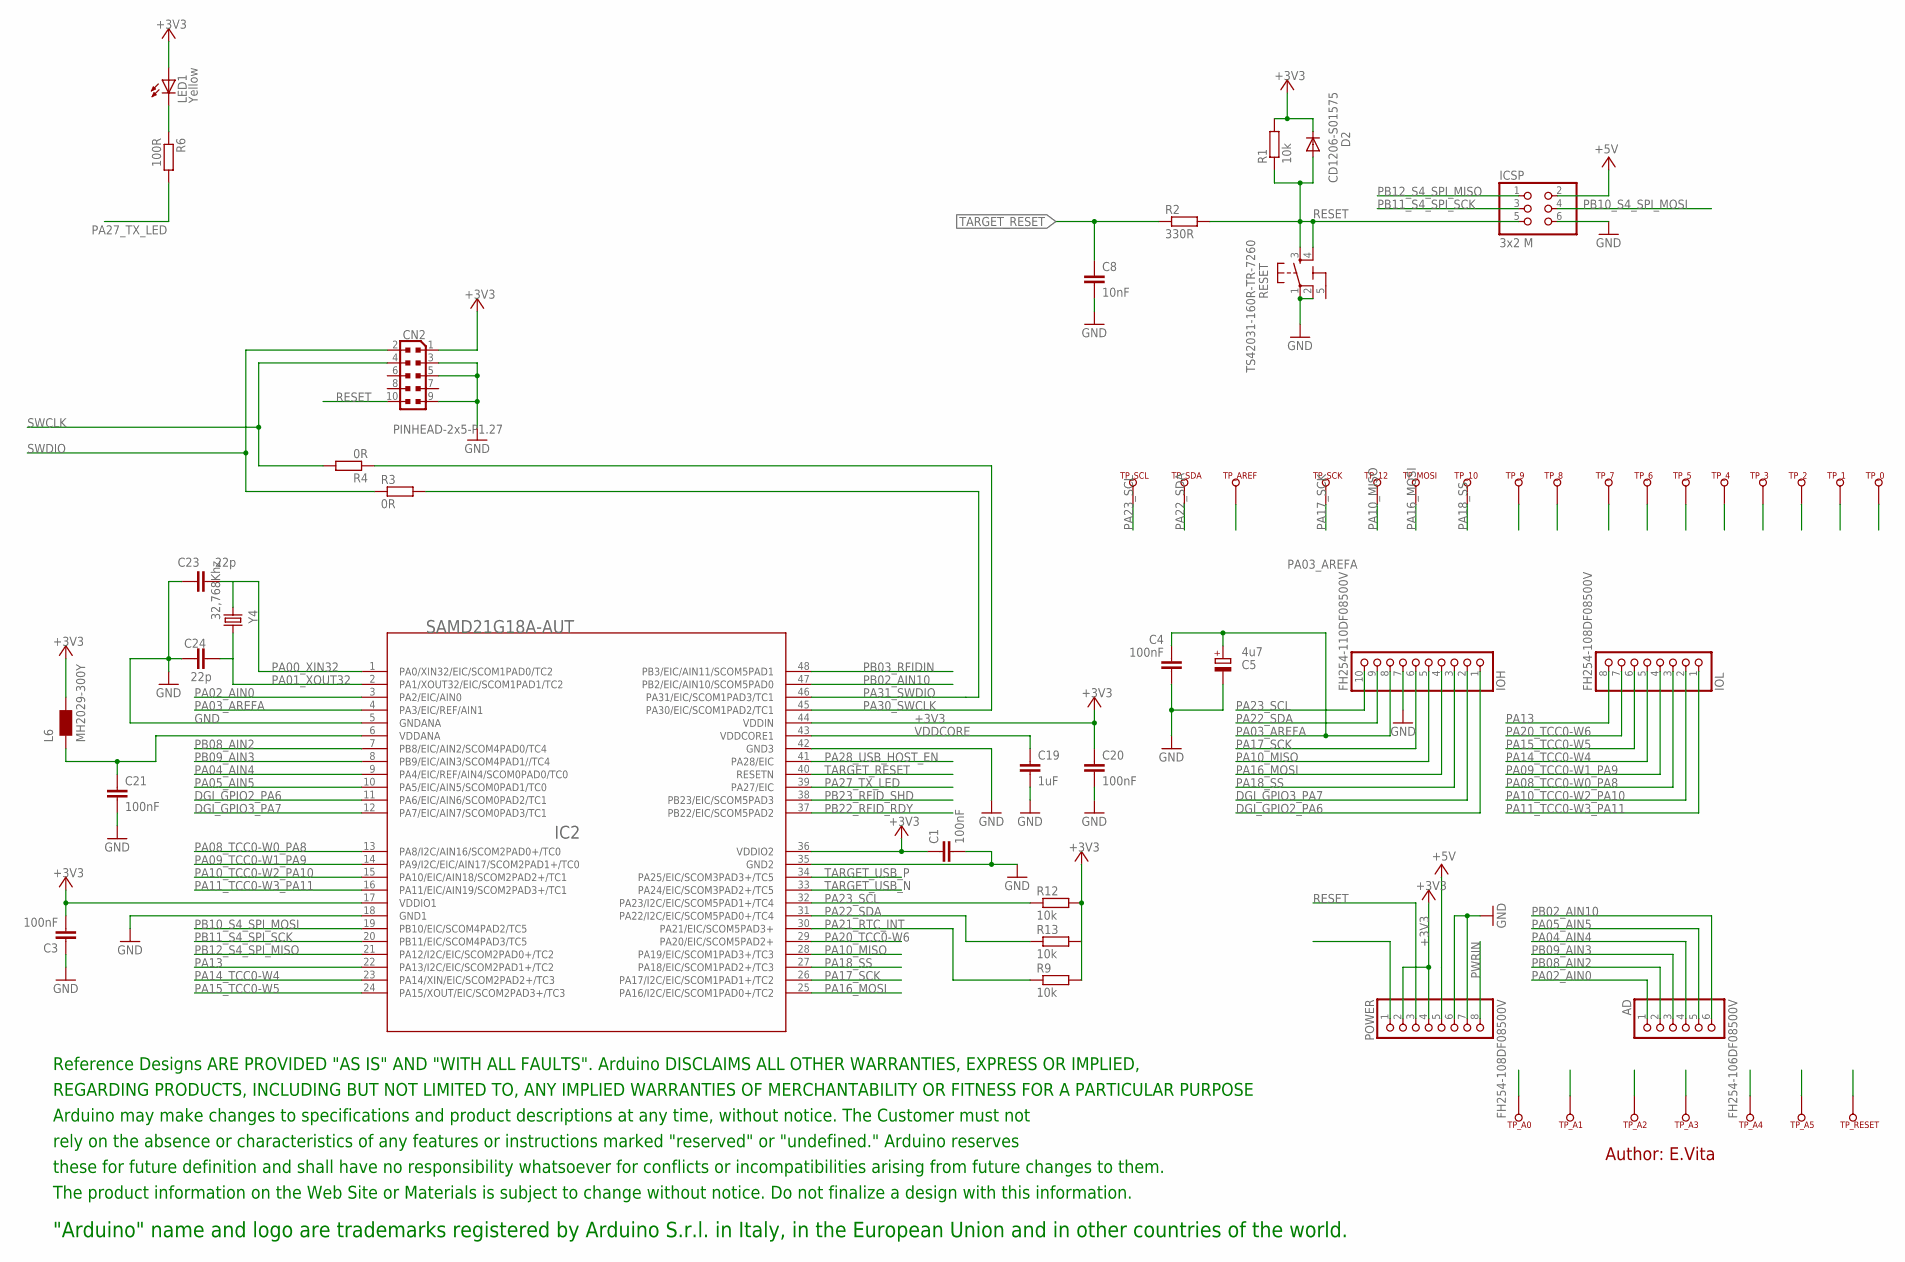
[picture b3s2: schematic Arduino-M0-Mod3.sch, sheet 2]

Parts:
AD: FH254-106DF08500V; 1X06
C1, C3, C4, C20, C21: 100nF; C0603-ROUND
C5: 4u7; SMC_A
C8: 10nF; C0603-ROUND
C19: 1uF; C0603-ROUND
C23, C24: 22p; C0603-ROUND
CN2: PINHEAD-2x5-P1.27; PINHEAD_2X05_127
D2: CD1206-S01575; MINIMELF
IC2: SAMD21G18A-AUT; TQFP48-7X7
ICSP: 3x2 M; 2X03
IOH: FH254-110DF08500V; 1X10
IOL: FH254-108DF08500V; 1X08
L6: MH2029-300Y; 0805
LED1: Yellow; CHIPLED_0805
POWER: FH254-108DF08500V; 1X08
R1, R9, R12, R13: 10k; R0603-ROUND
R2: 330R; R0603-ROUND
R3, R4: 0R; R0603-ROUND
R6: 100R; R0603-ROUND
RESET: TS42031-160R-TR-7260; TS42
TP_0, TP_1, TP_2, TP_3, TP_4, TP_5, TP_6, TP_7, TP_8, TP_9, TP_10, TP_12: TP_SP; TP-SP
TP_A0, TP_A1, TP_A2, TP_A3, TP_A4, TP_A5: TP_SP; TP-SP
TP_AREF: TP_SP; TP-SP
TP_MOSI: TP_SP; TP-SP
TP_RESET: TP_SP; TP-SP
TP_SCK: TP_SP; TP-SP
TP_SCL: TP_SP; TP-SP
TP_SDA: TP_SP; TP-SP
U$2: DISCLAIMER-SMALL; DISCLAIMER
Y4: 32,768Khz; RESONATOR_EPSON_FC_145

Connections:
5-GND: RESET.5 (5-GND)
+3V3: C1.1, C3.2, C20.1, CN2.1, D2.C, IC2.17 (VDDIO1), IC2.36 (VDDIO2), IC2.44 (VDDIN), L6.2, LED1.A, POWER.2, POWER.4, R1.2, R9.2, R12.2, R13.2; also elsewhere on the board
+5V: ICSP.2, POWER.5; also elsewhere on the board
DGI_GPIO1: TP_7.X
DGI_GPIO2_PA6: IC2.11 (PA6/EIC/AIN6/SCOM0PAD2/TC1), IOH.1, TP_8.X
DGI_GPIO3_PA7: IC2.12 (PA7/EIC/AIN7/SCOM0PAD3/TC1), IOH.2, TP_9.X
GND: C1.2, C3.1, C4.2, C5.-, C8.2, C19.2, C20.2, C21.2, C23.1, C24.1, CN2.3, CN2.5, CN2.9, IC2.5 (GNDANA), IC2.18 (GND1), IC2.35 (GND2), IC2.42 (GND3), ICSP.6, IOH.7, POWER.6, POWER.7, RESET.1, RESET.2; also elsewhere on the board
unnamed: LED1.C, R6.1
unnamed: C21.1, IC2.6 (VDDANA), L6.1
PA00_XIN32: C23.2, IC2.1 (PA0/XIN32/EIC/SCOM1PAD0/TC2), Y4.P$1 (1)
PA01_XOUT32: C24.2, IC2.2 (PA1/XOUT32/EIC/SCOM1PAD1/TC2), Y4.P$2 (2)
PA02_AIN0: AD.1, IC2.3 (PA2/EIC/AIN0), TP_A0.X
PA03_AREFA: C4.1, C5.+, IC2.4 (PA3/EIC/REF/AIN1), IOH.8, TP_AREF.X
PA04_AIN4: AD.4, IC2.9 (PA4/EIC/REF/AIN4/SCOM0PAD0/TC0), TP_A3.X
PA05_AIN5: AD.5, IC2.10 (PA5/EIC/AIN5/SCOM0PAD1/TC0), TP_A4.X
PA08_TCC0-W0_PA8: IC2.13 (PA8/I2C/AIN16/SCOM2PAD0+/TC0), IOL.3, TP_2.X
PA09_TCC0-W1_PA9: IC2.14 (PA9/I2C/EIC/AIN17/SCOM2PAD1+/TC0), IOL.4, TP_3.X
PA10_MISO: IC2.28 (PA19/EIC/SCOM1PAD3+/TC3), IOH.5, TP_12.X
PA10_TCC0-W2_PA10: IC2.15 (PA10/EIC/AIN18/SCOM2PAD2+/TC1), IOL.2, TP_1.X
PA11_TCC0-W3_PA11: IC2.16 (PA11/EIC/AIN19/SCOM2PAD3+/TC1), IOL.1, TP_0.X
PA13: IC2.22 (PA13/I2C/EIC/SCOM2PAD1+/TC2), IOL.8
PA14_TCC0-W4: IC2.23 (PA14/XIN/EIC/SCOM2PAD2+/TC3), IOL.5, TP_4.X
PA15_TCC0-W5: IC2.24 (PA15/XOUT/EIC/SCOM2PAD3+/TC3), IOL.6, TP_5.X
PA16_MOSI: IC2.25 (PA16/I2C/EIC/SCOM1PAD0+/TC2), IOH.4, TP_MOSI.X
PA17_SCK: IC2.26 (PA17/I2C/EIC/SCOM1PAD1+/TC2), IOH.6, TP_SCK.X
PA18_SS: IC2.27 (PA18/EIC/SCOM1PAD2+/TC3), IOH.3, TP_10.X
PA20_TCC0-W6: IC2.29 (PA20/EIC/SCOM5PAD2+), IOL.7, TP_6.X
PA21_RTC_INT: IC2.30 (PA21/EIC/SCOM5PAD3+), R9.1; also elsewhere on the board
PA22_SDA: IC2.31 (PA22/I2C/EIC/SCOM5PAD0+/TC4), IOH.9, R13.1, TP_SDA.X; also elsewhere on the board
PA23_SCL: IC2.32 (PA23/I2C/EIC/SCOM5PAD1+/TC4), IOH.10, R12.1, TP_SCL.X; also elsewhere on the board
PA27_TX_LED: IC2.39 (PA27/EIC), R6.2
PA28_USB_HOST_EN: IC2.41 (PA28/EIC); also elsewhere on the board
PA30_SWCLK: IC2.45 (PA30/EIC/SCOM1PAD2/TC1), R4.1
PA31_SWDIO: IC2.46 (PA31/EIC/SCOM1PAD3/TC1), R3.2
PB03_RFIDIN: IC2.48 (PB3/EIC/AIN11/SCOM5PAD1); also elsewhere on the board
PB08_AIN2: AD.2, IC2.7 (PB8/EIC/AIN2/SCOM4PAD0/TC4), TP_A1.X
PB09_AIN3: AD.3, IC2.8 (PB9/EIC/AIN3/SCOM4PAD1//TC4), TP_A2.X
PB10_S4_SPI_MOSI: IC2.19 (PB10/EIC/SCOM4PAD2/TC5), ICSP.4; also elsewhere on the board
PB11_S4_SPI_SCK: IC2.20 (PB11/EIC/SCOM4PAD3/TC5), ICSP.3; also elsewhere on the board
PB12_S4_SPI_MISO: IC2.21 (PA12/I2C/EIC/SCOM2PAD0+/TC2), ICSP.1; also elsewhere on the board
PB22_RFID_RDY: IC2.37 (PB22/EIC/SCOM5PAD2); also elsewhere on the board
PB23_RFID_SHD: IC2.38 (PB23/EIC/SCOM5PAD3); also elsewhere on the board
PWRIN: POWER.8; also elsewhere on the board
RESET: CN2.10, D2.A, ICSP.5, POWER.3, R1.1, R2.2, RESET.3, RESET.4, TP_RESET.X
SWCLK: CN2.4, R4.2
SWDIO: CN2.2, R3.1
TARGET_RESET: C8.1, IC2.40 (RESETN), R2.1
TARGET_USB_N: IC2.33 (PA24/EIC/SCOM3PAD2+/TC5); also elsewhere on the board
TARGET_USB_P: IC2.34 (PA25/EIC/SCOM3PAD3+/TC5); also elsewhere on the board
VDDCORE: C19.1, IC2.43 (VDDCORE1)

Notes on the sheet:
Author: E.Vita

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

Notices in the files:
parts and their libraries:
SparkFun-DigitalIC: Licensing: Creative Commons ShareAlike 4.0 International - https://creativecommons.org/licenses/by-sa/4.0
